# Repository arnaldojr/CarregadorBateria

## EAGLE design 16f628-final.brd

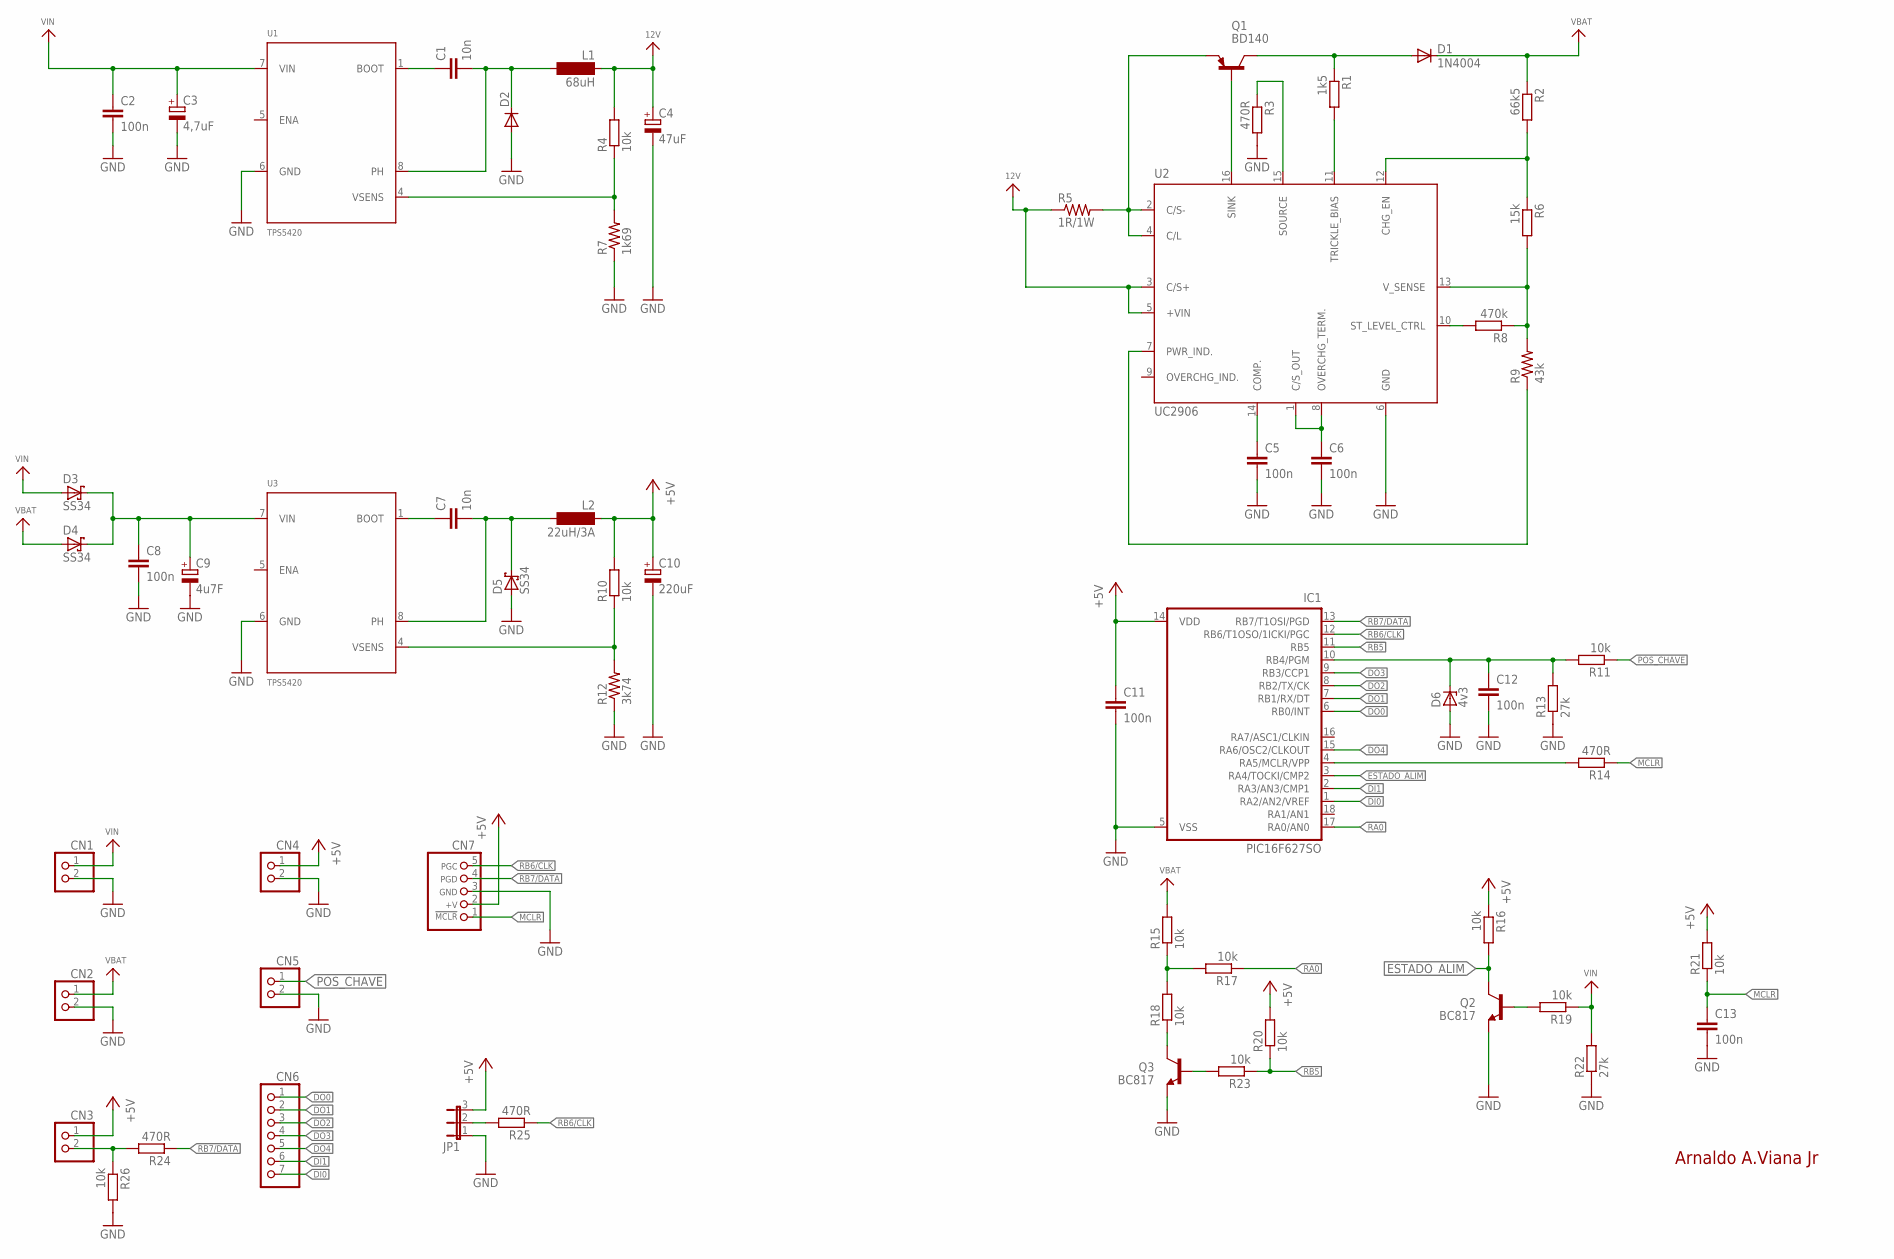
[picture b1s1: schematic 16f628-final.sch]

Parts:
C1, C7: 10n; C0805
C2, C5, C6, C8, C11, C12, C13: 100n; C0805
C3: 4,7uF; E2,5-6
C4: 47uF; E2,5-6
C9: 4u7F; E2,5-6
C10: 220uF; E2,5-6
CN1, CN2, CN3, CN4, CN5: HEADER-1X2ROUND; 1X02_ROUND
CN6: HEADER-1X7ROUND; 1X07_ROUND
CN7: CON_HEADER_PRG_PIC_ICSP0.1INCH_A; HEADER_PRG_1X05
D1: 1N4004; DO41-10
D2: DIODE-SOD123; SOD123
D3, D4, D5: SS34; SMC
D6: 4v3; SOT23
IC1: PIC16F627SO; SO-18W; MPN PIC16F627-04/SO
JP1: JUMPER3
L1: 68uH; SD12K100
L2: 22uH/3A; SD12K100
Q1: BD140; TO126
Q2, Q3: BC817; SOT23-BEC
R1: 1k5; R0805
R2: 66k5; R0805
R3, R14, R24, R25: 470R; R0805
R4, R10, R11, R15, R16, R17, R18, R19, R20, R21, R23, R26: 10k; R0805
R5: 1R/1W; 0805-THM
R6: 15k; R0805
R7: 1k69; 0805-THM
R8: 470k; R0805
R9: 43k; 0805-THM
R12: 3k74; 0805-THM
R13, R22: 27k; R0805
U1, U3: TPS5420; SOIC8_150MIL
U2: UC2906; SOIC_16

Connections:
12V: C4.+, L1.1, R4.2, R5.1, U2.3 (C/S+), U2.5 (+VIN)
+5V: C10.+, C11.1, CN3.1, CN4.1, CN7.2 (+V), IC1.14 (VDD), JP1.3, L2.1, R10.2, R16.1, R20.2, R21.2
DI0: CN6.7, IC1.1 (RA2/AN2/VREF)
DI1: CN6.6, IC1.2 (RA3/AN3/CMP1)
DO0: CN6.1, IC1.6 (RB0/INT)
DO1: CN6.2, IC1.7 (RB1/RX/DT)
DO2: CN6.3, IC1.8 (RB2/TX/CK)
DO3: CN6.4, IC1.9 (RB3/CCP1)
DO4: CN6.5, IC1.15 (RA6/OSC2/CLKOUT)
ESTADO_ALIM: IC1.3 (RA4/TOCKI/CMP2), Q2.C, R16.2
GND: C2.2, C3.-, C4.-, C5.2, C6.2, C8.2, C9.-, C10.-, C11.2, C12.2, C13.2, CN1.2, CN2.2, CN4.2, CN5.2, CN7.3 (GND), D2.A, D5.A, D6.1 (A), IC1.5 (VSS), JP1.1, Q2.E, Q3.E, R3.2, R7.1, R12.1, R13.1, R22.1, R26.2, U1.6 (GND), U2.6 (GND), U3.6 (GND)
MCLR: C13.1, CN7.1 (/MCLR), R14.1, R21.1
unnamed: C6.1, U2.1 (C/S_OUT), U2.8 (OVERCHG_TERM.)
unnamed: IC1.4 (RA5/MCLR/VPP), R14.2
unnamed: CN3.2, R24.2, R26.1
unnamed: C5.1, U2.14 (COMP.)
unnamed: R9.1, U2.7 (PWR_IND.)
unnamed: R3.1, U2.15 (SOURCE)
unnamed: C7.1, U3.1 (BOOT)
unnamed: R2.2, R6.1, U2.12 (CHG_EN)
unnamed: R1.2, U2.11 (TRICKLE_BIAS)
unnamed: Q1.3 (B), U2.16 (SINK)
unnamed: D1.A, Q1.2 (C), R1.1
unnamed: R6.2, R8.1, R9.2, U2.13 (V_SENSE)
unnamed: R8.2, U2.10 (ST_LEVEL_CTRL)
unnamed: C1.1, U1.1 (BOOT)
unnamed: Q3.B, R23.2
unnamed: Q3.C, R18.1
unnamed: Q1.1 (E), R5.2, U2.2 (C/S-), U2.4 (C/L)
unnamed: R10.1, R12.2, U3.4 (VSENS)
unnamed: C7.2, D5.C, L2.2, U3.8 (PH)
unnamed: R4.1, R7.2, U1.4 (VSENS)
unnamed: JP1.2, R25.2
unnamed: C8.1, C9.+, D3.C, D4.C, U3.7 (VIN)
unnamed: C1.2, D2.C, L1.2, U1.8 (PH)
unnamed: R15.1, R17.2, R18.2
unnamed: C12.1, D6.3 (C), IC1.10 (RB4/PGM), R11.2, R13.2
unnamed: Q2.B, R19.2
POS_CHAVE: CN5.1, R11.1
RA0: IC1.17 (RA0/AN0), R17.1
RB5: IC1.11 (RB5), R20.1, R23.1
RB6/CLK: CN7.5 (PGC), IC1.12 (RB6/T1OSO/1ICKI/PGC), R25.1
RB7/DATA: CN7.4 (PGD), IC1.13 (RB7/T1OSI/PGD), R24.1
VBAT: CN2.1, D1.C, D4.A, R2.1, R15.2
VIN: C2.1, C3.+, CN1.1, D3.A, R19.1, R22.2, U1.7 (VIN)

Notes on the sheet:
Arnaldo A.Viana Jr

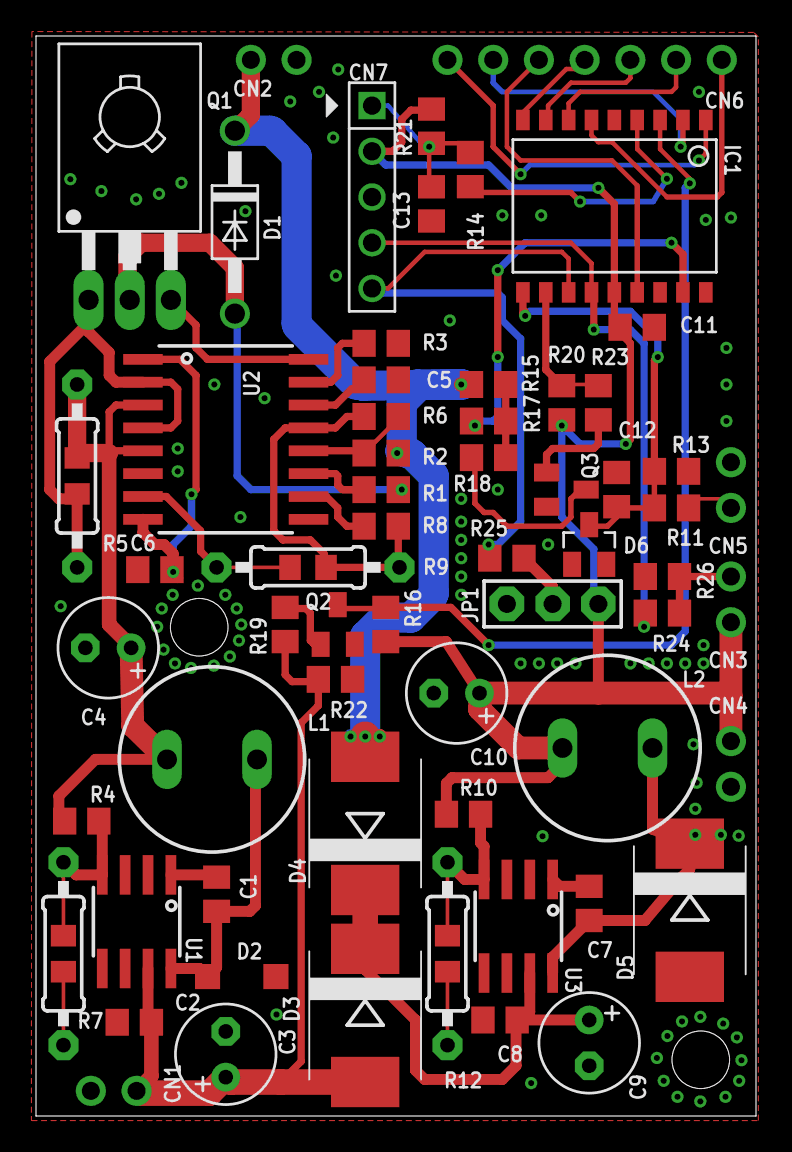
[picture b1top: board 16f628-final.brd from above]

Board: 2 copper layers, 40.0 x 60.0 mm, 62 parts (0 on the bottom side), 45 nets.

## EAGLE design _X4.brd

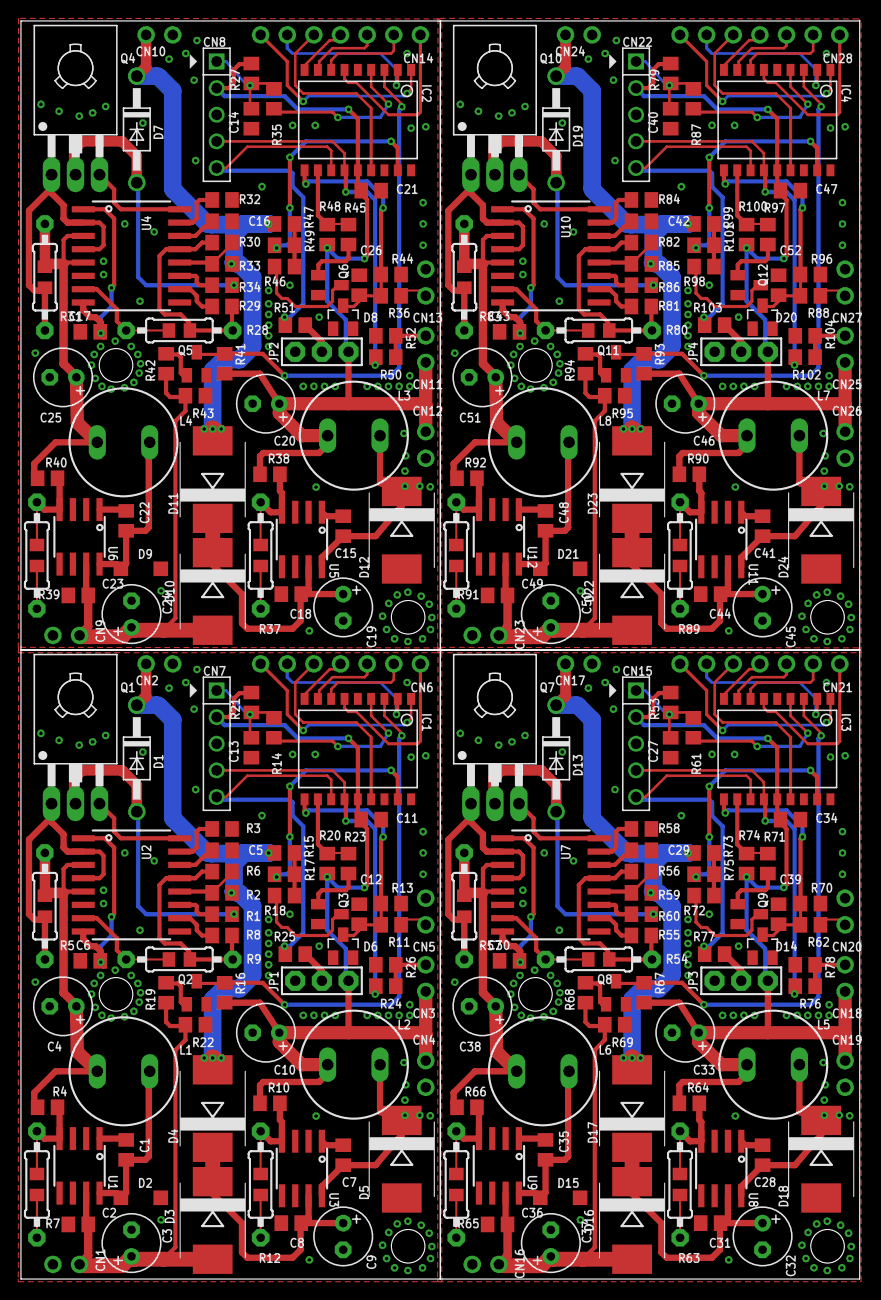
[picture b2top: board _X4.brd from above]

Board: 2 copper layers, 80.0 x 120.0 mm, 248 parts (0 on the bottom side), 180 nets.

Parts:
C1, C7, C15, C22, C28, C35, C41, C48: 10n; C0805
C2, C5, C6, C8, C11, C12, C13, C14, C16, C17, C18, C21, C23, C26, C27, C29, C30, C31, C34, C36, C39, C40, C42, C43, C44, C47, C49, C52: 100n; C0805
C3, C24, C37, C50: 4,7uF; E2,5-6
C4, C25, C38, C51: 47uF; E2,5-6
C9, C19, C32, C45: 4u7F; E2,5-6
C10, C20, C33, C46: 220uF; E2,5-6
CN1, CN2, CN3, CN4, CN5, CN9, CN10, CN11, CN12, CN13, CN16, CN17, CN18, CN19, CN20, CN23, CN24, CN25, CN26, CN27: 1X02_ROUND
CN6, CN14, CN21, CN28: 1X07_ROUND
CN7, CN8, CN15, CN22: CON_HEADER_PRG_PIC_ICSP0.1INCH_A; HEADER_PRG_1X05
D1, D7, D13, D19: 1N4004; DO41-10
D2, D9, D15, D21: SOD123
D3, D4, D5, D10, D11, D12, D16, D17, D18, D22, D23, D24: SS34; SMC
D6, D8, D14, D20: 4v3; SOT23
IC1, IC2, IC3, IC4: PIC16F627SO; SO-18W
JP1, JP2, JP3, JP4: JUMPER3
L1, L4, L6, L8: 68uH; SD12K100
L2, L3, L5, L7: 22uH/3A; SD12K100
Q1, Q4, Q7, Q10: BD140; TO126
Q2, Q3, Q5, Q6, Q8, Q9, Q11, Q12: BC817; SOT23-BEC
R1, R34, R60, R86: 1k5; R0805
R2, R33, R59, R85: 66k5; R0805
R3, R14, R24, R25, R32, R35, R50, R51, R58, R61, R76, R77, R84, R87, R102, R103: 470R; R0805
R4, R10, R11, R15, R16, R17, R18, R19, R20, R21, R23, R26, R27, R36, R38, R40, R41, R42, R45, R46, R47, R48, R49, R52, R53, R62, R64, R66, R67, R68, R71, R72, R73, R74, R75, R78, R79, R88, R90, R92, R93, R94, R97, R98, R99, R100, R101, R104: 10k; R0805
R5, R31, R57, R83: 1R/1W; 0805-THM
R6, R30, R56, R82: 15k; R0805
R7, R39, R65, R91: 1k69; 0805-THM
R8, R29, R55, R81: 470k; R0805
R9, R28, R54, R80: 43k; 0805-THM
R12, R37, R63, R89: 3k74; 0805-THM
R13, R22, R43, R44, R69, R70, R95, R96: 27k; R0805
U1, U3, U5, U6, U8, U9, U11, U12: TPS5420; SOIC8_150MIL
U2, U4, U7, U10: UC2906; SOIC_16

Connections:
12V: C4.+, L1.1, R4.2, R5.1, U2.3, U2.5
12V1: C25.+, L4.1, R31.1, R40.2, U4.3, U4.5
12V2: C38.+, L6.1, R57.1, R66.2, U7.3, U7.5
12V3: C51.+, L8.1, R83.1, R92.2, U10.3, U10.5
+5V: C10.+, C11.1, CN3.1, CN4.1, CN7.2, IC1.14, JP1.3, L2.1, R10.2, R16.1, R20.2, R21.2
+5V1: C20.+, C21.1, CN8.2, CN11.1, CN12.1, IC2.14, JP2.3, L3.1, R27.2, R38.2, R41.1, R48.2
+5V2: C33.+, C34.1, CN15.2, CN18.1, CN19.1, IC3.14, JP3.3, L5.1, R53.2, R64.2, R67.1, R74.2
+5V3: C46.+, C47.1, CN22.2, CN25.1, CN26.1, IC4.14, JP4.3, L7.1, R79.2, R90.2, R93.1, R100.2
DI0: CN6.7, IC1.1
DI1: CN6.6, IC1.2
DI2: CN14.7, IC2.1
DI3: CN14.6, IC2.2
DI4: CN21.7, IC3.1
DI5: CN21.6, IC3.2
DI6: CN28.7, IC4.1
DI7: CN28.6, IC4.2
DO0: CN6.1, IC1.6
DO1: CN6.2, IC1.7
DO2: CN6.3, IC1.8
DO3: CN6.4, IC1.9
DO4: CN6.5, IC1.15
DO5: CN14.4, IC2.9
DO6: CN14.5, IC2.15
DO7: CN14.1, IC2.6
DO8: CN14.2, IC2.7
DO9: CN14.3, IC2.8
DO10: CN21.4, IC3.9
DO11: CN21.5, IC3.15
DO12: CN21.1, IC3.6
DO13: CN21.2, IC3.7
DO14: CN21.3, IC3.8
DO15: CN28.4, IC4.9
DO16: CN28.5, IC4.15
DO17: CN28.1, IC4.6
DO18: CN28.2, IC4.7
DO19: CN28.3, IC4.8
ESTADO_ALIM: IC1.3, Q2.C, R16.2
ESTADO_ALIM1: IC2.3, Q5.C, R41.2
ESTADO_ALIM2: IC3.3, Q8.C, R67.2
ESTADO_ALIM3: IC4.3, Q11.C, R93.2
GND: C2.2, C3.-, C4.-, C5.2, C6.2, C8.2, C9.-, C10.-, C11.2, C12.2, C13.2, CN1.2, CN2.2, CN4.2, CN5.2, CN7.3, D2.A, D5.A, D6.1, IC1.5, JP1.1, Q2.E, Q3.E, R3.2, R7.1, R12.1, R13.1, R22.1, R26.2, U1.6, U2.6, U3.6
GND1: C14.2, C16.2, C17.2, C18.2, C19.-, C20.-, C21.2, C23.2, C24.-, C25.-, C26.2, CN8.3, CN9.2, CN10.2, CN12.2, CN13.2, D8.1, D9.A, D12.A, IC2.5, JP2.1, Q5.E, Q6.E, R32.2, R37.1, R39.1, R43.1, R44.1, R52.2, U4.6, U5.6, U6.6
GND2: C27.2, C29.2, C30.2, C31.2, C32.-, C33.-, C34.2, C36.2, C37.-, C38.-, C39.2, CN15.3, CN16.2, CN17.2, CN19.2, CN20.2, D14.1, D15.A, D18.A, IC3.5, JP3.1, Q8.E, Q9.E, R58.2, R63.1, R65.1, R69.1, R70.1, R78.2, U7.6, U8.6, U9.6
GND3: C40.2, C42.2, C43.2, C44.2, C45.-, C46.-, C47.2, C49.2, C50.-, C51.-, C52.2, CN22.3, CN23.2, CN24.2, CN26.2, CN27.2, D20.1, D21.A, D24.A, IC4.5, JP4.1, Q11.E, Q12.E, R84.2, R89.1, R91.1, R95.1, R96.1, R104.2, U10.6, U11.6, U12.6
MCLR: C13.1, CN7.1, R14.1, R21.1
MCLR1: C14.1, CN8.1, R27.1, R35.1
MCLR2: C27.1, CN15.1, R53.1, R61.1
MCLR3: C40.1, CN22.1, R79.1, R87.1
unnamed: C6.1, U2.1, U2.8
unnamed: IC1.4, R14.2
unnamed: CN3.2, R24.2, R26.1
unnamed: C5.1, U2.14
unnamed: R9.1, U2.7
unnamed: R3.1, U2.15
unnamed: C7.1, U3.1
unnamed: R2.2, R6.1, U2.12
unnamed: R1.2, U2.11
unnamed: Q1.3, U2.16
unnamed: D1.A, Q1.2, R1.1
unnamed: R6.2, R8.1, R9.2, U2.13
unnamed: R8.2, U2.10
unnamed: C1.1, U1.1
unnamed: Q3.B, R23.2
unnamed: Q3.C, R18.1
unnamed: Q1.1, R5.2, U2.2, U2.4
unnamed: R10.1, R12.2, U3.4
unnamed: C7.2, D5.C, L2.2, U3.8
unnamed: R4.1, R7.2, U1.4
unnamed: JP1.2, R25.2
unnamed: C8.1, C9.+, D3.C, D4.C, U3.7
unnamed: C1.2, D2.C, L1.2, U1.8
unnamed: R15.1, R17.2, R18.2
unnamed: C12.1, D6.3, IC1.10, R11.2, R13.2
unnamed: Q4.3, U4.16
unnamed: D7.A, Q4.2, R34.1
unnamed: R28.2, R29.1, R30.2, U4.13
unnamed: R29.2, U4.10
unnamed: Q2.B, R19.2
unnamed: R28.1, U4.7
unnamed: R32.1, U4.15
unnamed: R30.1, R33.2, U4.12
unnamed: R34.2, U4.11
unnamed: IC2.4, R35.2
unnamed: C26.1, D8.3, IC2.10, R36.2, R44.2
unnamed: Q6.B, R45.2
unnamed: Q6.C, R46.1
unnamed: C16.1, U4.14
unnamed: C17.1, U4.1, U4.8
unnamed: Q4.1, R31.2, U4.2, U4.4
unnamed: C15.1, U5.1
unnamed: R37.2, R38.1, U5.4
unnamed: C15.2, D12.C, L3.2, U5.8
unnamed: C18.1, C19.+, D10.C, D11.C, U5.7
unnamed: C22.1, U6.1
unnamed: R39.2, R40.1, U6.4
unnamed: C22.2, D9.C, L4.2, U6.8
unnamed: Q5.B, R42.2
unnamed: R46.2, R47.1, R49.2
unnamed: CN11.2, R50.2, R52.1
unnamed: JP2.2, R51.2
unnamed: Q7.3, U7.16
unnamed: D13.A, Q7.2, R60.1
unnamed: R54.2, R55.1, R56.2, U7.13
unnamed: R55.2, U7.10
unnamed: R54.1, U7.7
unnamed: R58.1, U7.15
unnamed: R56.1, R59.2, U7.12
unnamed: R60.2, U7.11
unnamed: IC3.4, R61.2
unnamed: C39.1, D14.3, IC3.10, R62.2, R70.2
unnamed: Q9.B, R71.2
unnamed: Q9.C, R72.1
unnamed: C29.1, U7.14
unnamed: C30.1, U7.1, U7.8
unnamed: Q7.1, R57.2, U7.2, U7.4
unnamed: C28.1, U8.1
unnamed: R63.2, R64.1, U8.4
unnamed: C28.2, D18.C, L5.2, U8.8
unnamed: C31.1, C32.+, D16.C, D17.C, U8.7
unnamed: C35.1, U9.1
unnamed: R65.2, R66.1, U9.4
unnamed: C35.2, D15.C, L6.2, U9.8
unnamed: Q8.B, R68.2
unnamed: R72.2, R73.1, R75.2
unnamed: CN18.2, R76.2, R78.1
unnamed: JP3.2, R77.2
unnamed: Q10.3, U10.16
unnamed: D19.A, Q10.2, R86.1
unnamed: R80.2, R81.1, R82.2, U10.13
unnamed: R81.2, U10.10
unnamed: R80.1, U10.7
unnamed: R84.1, U10.15
unnamed: R82.1, R85.2, U10.12
unnamed: R86.2, U10.11
unnamed: IC4.4, R87.2
unnamed: C52.1, D20.3, IC4.10, R88.2, R96.2
unnamed: Q12.B, R97.2
unnamed: Q12.C, R98.1
unnamed: C42.1, U10.14
unnamed: C43.1, U10.1, U10.8
unnamed: Q10.1, R83.2, U10.2, U10.4
unnamed: C41.1, U11.1
unnamed: R89.2, R90.1, U11.4
unnamed: C41.2, D24.C, L7.2, U11.8
unnamed: C44.1, C45.+, D22.C, D23.C, U11.7
unnamed: C48.1, U12.1
unnamed: R91.2, R92.1, U12.4
unnamed: C48.2, D21.C, L8.2, U12.8
unnamed: Q11.B, R94.2
unnamed: R98.2, R99.1, R101.2
unnamed: CN25.2, R102.2, R104.1
unnamed: JP4.2, R103.2
POS_CHAVE: CN5.1, R11.1
POS_CHAVE1: CN13.1, R36.1
POS_CHAVE2: CN20.1, R62.1
POS_CHAVE3: CN27.1, R88.1
RA0: IC1.17, R17.1
RA1: IC2.17, R49.1
RA2: IC3.17, R75.1
RA3: IC4.17, R101.1
RB1: IC2.11, R45.1, R48.1
RB2: IC3.11, R71.1, R74.1
RB3: IC4.11, R97.1, R100.1
RB5: IC1.11, R20.1, R23.1
RB6/CLK: CN7.5, IC1.12, R25.1
RB6/CLK1: CN8.5, IC2.12, R51.1
RB6/CLK2: CN15.5, IC3.12, R77.1
RB6/CLK3: CN22.5, IC4.12, R103.1
RB7/DATA: CN7.4, IC1.13, R24.1
RB7/DATA1: CN8.4, IC2.13, R50.1
RB7/DATA2: CN15.4, IC3.13, R76.1
RB7/DATA3: CN22.4, IC4.13, R102.1
VBAT: CN2.1, D1.C, D4.A, R2.1, R15.2
VBAT1: CN10.1, D7.C, D11.A, R33.1, R47.2
VBAT2: CN17.1, D13.C, D17.A, R59.1, R73.2
VBAT3: CN24.1, D19.C, D23.A, R85.1, R99.2
VIN: C2.1, C3.+, CN1.1, D3.A, R19.1, R22.2, U1.7
VIN1: C23.1, C24.+, CN9.1, D10.A, R42.1, R43.2, U6.7
VIN2: C36.1, C37.+, CN16.1, D16.A, R68.1, R69.2, U9.7
VIN3: C49.1, C50.+, CN23.1, D22.A, R94.1, R95.2, U12.7

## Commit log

2018-11-02 commit inicial
